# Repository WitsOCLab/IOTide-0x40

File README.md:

# IOTide-0x40
STM32 board with 64 powerful outputs to drive up to 16 (0x40) stepper motors.

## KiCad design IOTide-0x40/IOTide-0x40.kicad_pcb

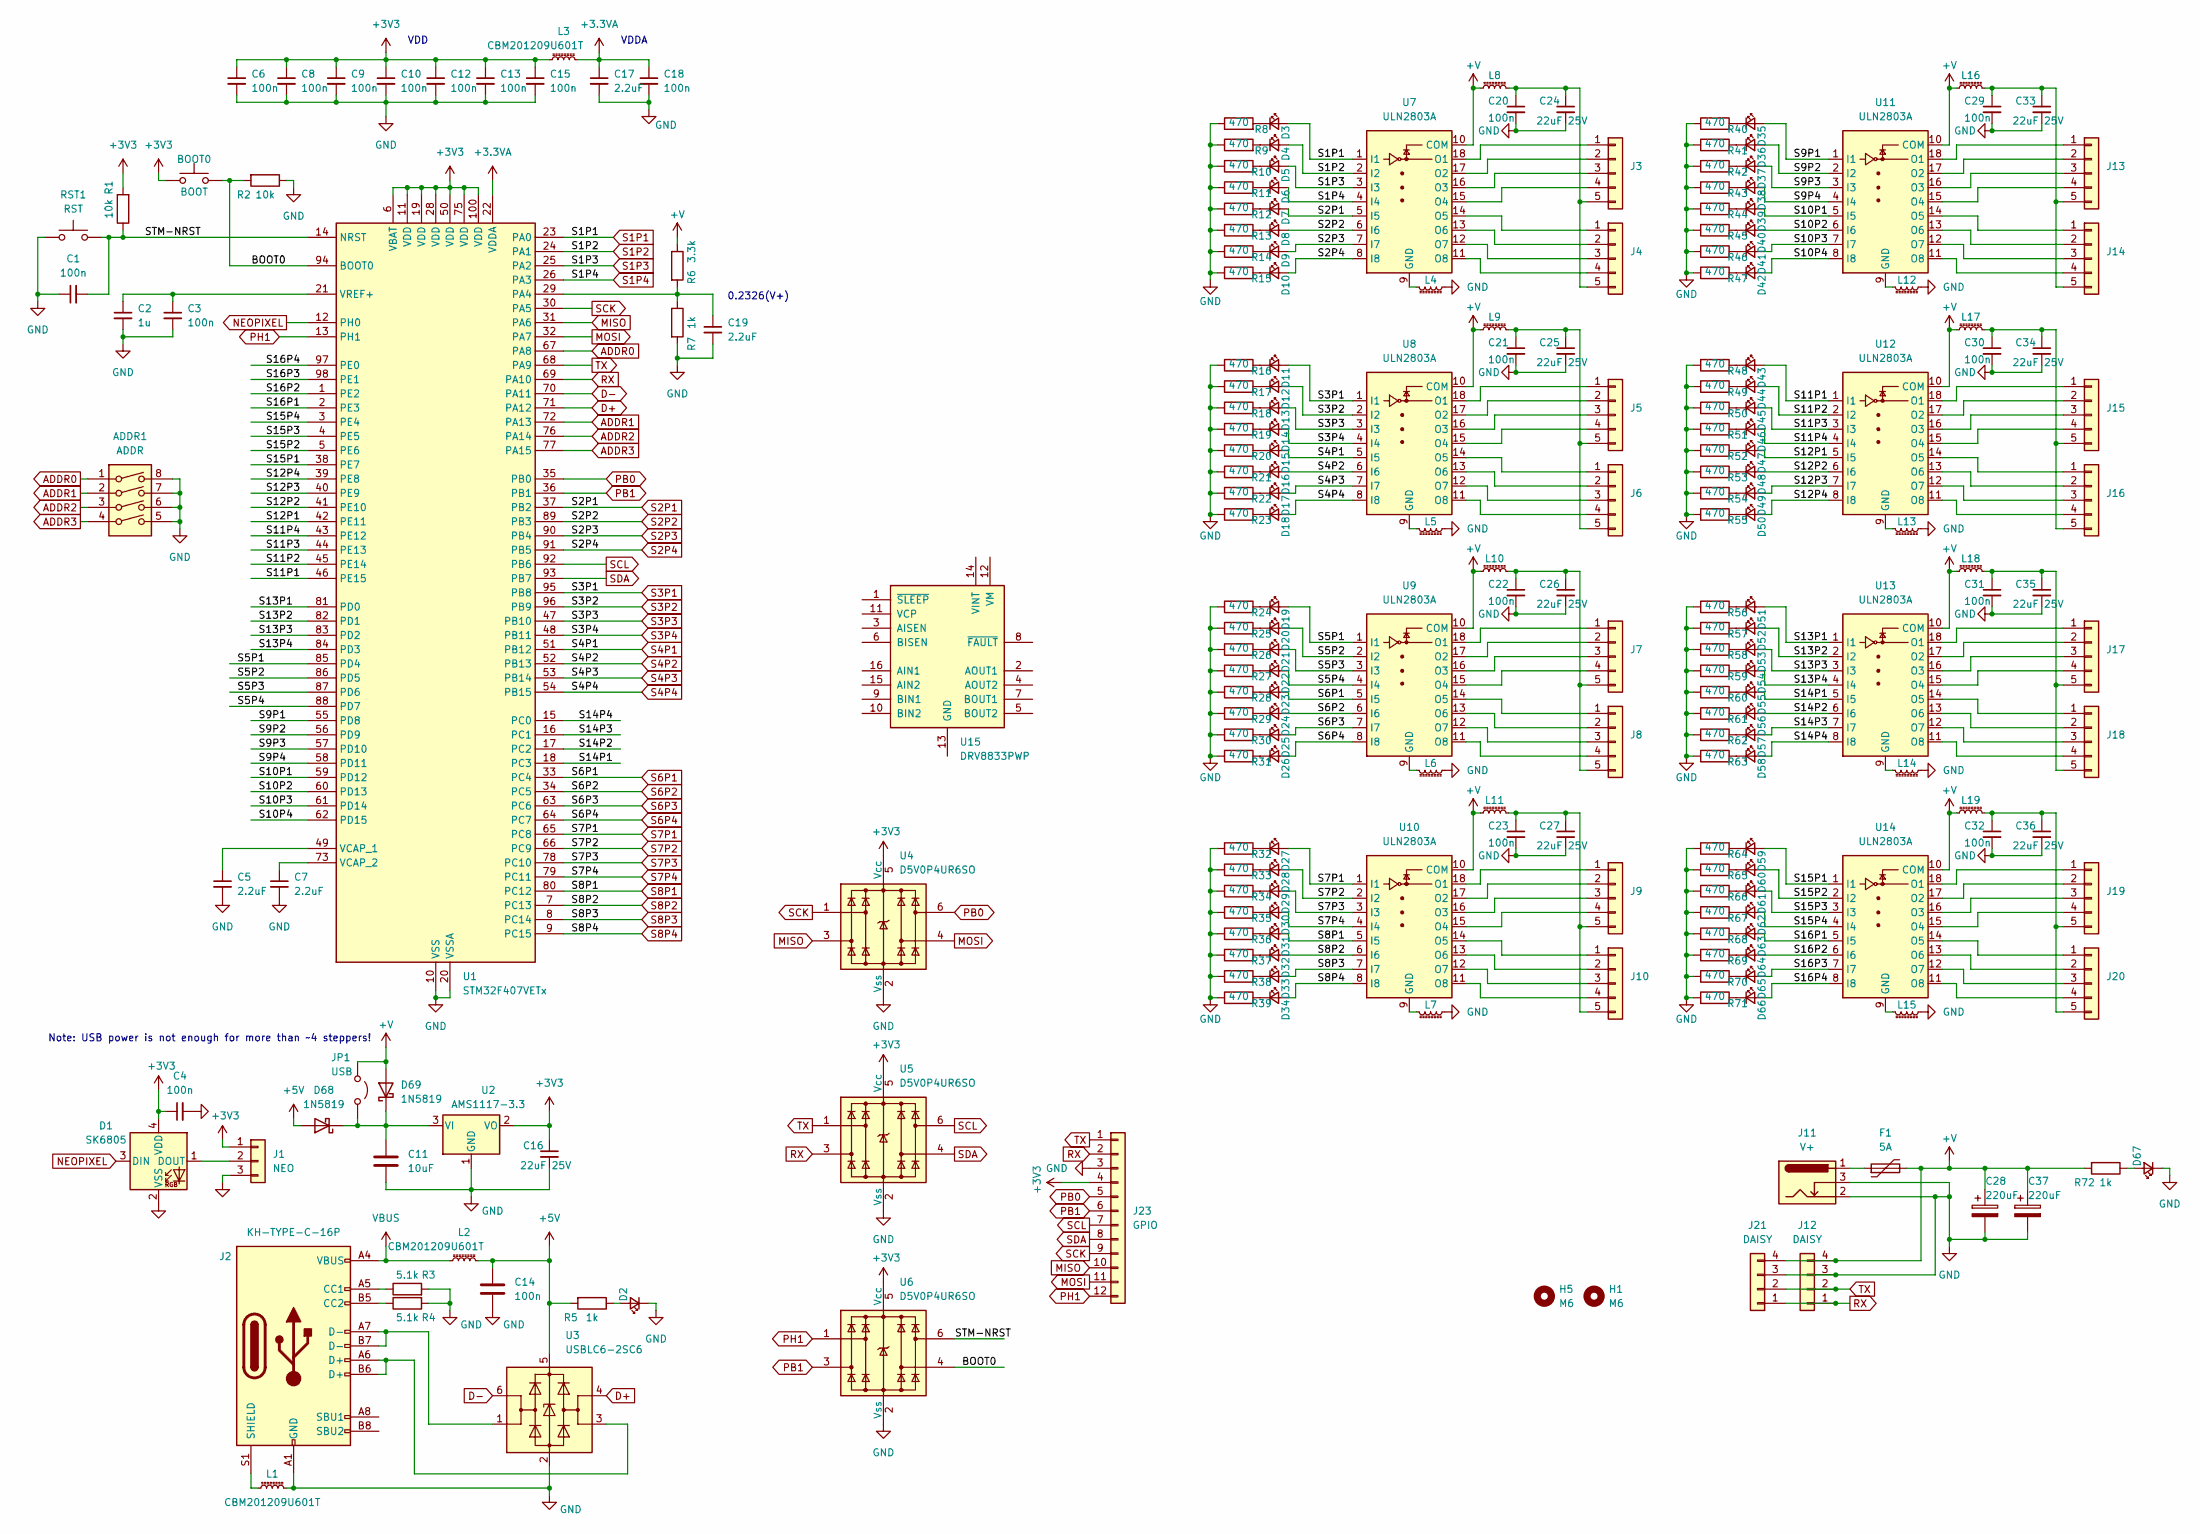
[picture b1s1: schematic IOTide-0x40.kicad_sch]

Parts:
ADDR1: ADDR; SW_DIP_SPSTx04_Slide_6.7x11.72mm_W6.73mm_P2.54mm_LowProfile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; LCSC C6331176
BOOT0: BOOT; SW_SPST_B3U-1000P-B; LCSC C720477
C1, C3, C4, C6, C8, C9, C10, C12, C13, C14, C15, C18, C20, C21, C22, C23, C29, C30, C31, C32: 100n; C_0402_1005Metric; LCSC C1525
C2: 1u; C_0402_1005Metric; LCSC C52923
C5, C7, C17, C19: 2.2uF; C_0402_1005Metric; LCSC C12530
C11: 10uF; C_0603_1608Metric; LCSC C96446
C16, C24, C25, C26, C27, C33, C34, C35, C36: 22uF 25V; C_0805_2012Metric; LCSC C45783
C28, C37: 220uF; CP_Elec_6.3x7.7; LCSC C7471881
D1: SK6805; LED_SK6805_PLCC4_2.4x2.7mm_P1.3mm; LCSC C2909056
D2, D67: BLUE; LED_0402_1005Metric; LCSC C130724
D3, D4, D5, D6, D7, D8, D9, D10, D11, D12, D13, D14, D15, D16, D17, D18, D19, D20, D21, D22, D23, D24, D25, D26, D27, D28, D29, D30, D31, D32, D33, D34, D35, D36, D37, D38, D39, D40, D41, D42, D43, D44, D45, D46, D47, D48, D49, D50, D51, D52, D53, D54, D55, D56, D57, D58, D59, D60, D61, D62, D63, D64, D65, D66: LED_Small; LED_0402_1005Metric; LCSC C130719
D68, D69: 1N5819; D_SOD-323; LCSC C191023
F1: 5A; Fuse_2920_7451Metric_Pad2.10x5.45mm_HandSolder; LCSC C20539728
H1, H5: M6; MountingHole_6.4mm_M6
J1: NEO; PinHeader_1x03_P2.54mm_Vertical
J2: KH-TYPE-C-16P; USB_C_Receptacle_GCT_USB4105-xx-A_16P_TopMnt_Horizontal; JLC C709357
J3: S1; JST_XH_B5B-XH-A_1x05_P2.50mm_Vertical; LCSC C161872
J4: S2; JST_XH_B5B-XH-A_1x05_P2.50mm_Vertical; LCSC C161872
J5, J6, J7, J8, J9, J10, J13, J14, J15, J16, J17, J18, J19, J20: Conn_01x05; JST_XH_B5B-XH-A_1x05_P2.50mm_Vertical; LCSC C161872
J11: V+; BarrelJack_Horizontal
J12, J21: DAISY; PinSocket_1x04_P2.54mm_Vertical
J23: GPIO; PinHeader_1x12_P2.54mm_Vertical
JP1: USB; SolderJumper-2_P1.3mm_Open_TrianglePad1.0x1.5mm
L1, L2, L3, L4, L5, L6, L7, L8, L9, L10, L11, L12, L13, L14, L15, L16, L17, L18, L19: CBM201209U601T; C_0805_2012Metric; LCSC C139168
R1, R2: 10k; R_0402_1005Metric; LCSC C25744
R3, R4: 5.1k; R_0402_1005Metric; LCSC C25905
R5, R72: 1k; R_0402_1005Metric; LCSC C25744
R6: 3.3k; R_0402_1005Metric; LCSC C25890
R7: 1k; R_0402_1005Metric; LCSC C11702
R8, R9, R10, R11, R12, R13, R14, R15, R16, R17, R18, R19, R20, R21, R22, R23, R24, R25, R26, R27, R28, R29, R30, R31, R32, R33, R34, R35, R36, R37, R38, R39, R40, R41, R42, R43, R44, R45, R46, R47, R48, R49, R50, R51, R52, R53, R54, R55, R56, R57, R58, R59, R60, R61, R62, R63, R64, R65, R66, R67, R68, R69, R70, R71: 470; R_0402_1005Metric; LCSC C25167
RST1: RST; SW_SPST_B3U-1000P-B; LCSC C720477
U1: STM32F407VETx; LQFP-100_14x14mm_P0.5mm; LCSC C28730
U2: AMS1117-3.3; SOT-89-3; LCSC C5120796
U3: USBLC6-2SC6; SOT-23-6; LCSC C2827654
U4, U5, U6: D5V0P4UR6SO; SOT-23-6; LCSC C531179
U7, U8, U9, U10, U11, U12, U13, U14: ULN2803A; SOP-18_7.495x11.515mm_P1.27mm; LCSC C845537
U15: DRV8833PWP; HTSSOP-16-1EP_4.4x5mm_P0.65mm_EP3.4x5mm_Mask2.46x2.31mm_The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

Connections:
+3.3VA: C17.1, C18.1, L3.2, U1.22 (VDDA)
+3V3: BOOT0.1, C4.1, C6.1, C8.1, C9.1, C10.1, C12.1, C13.1, C15.1, C16.1, D1.4 (VDD), J1.1, J23.4, L3.1, R1.2, U1.6 (VBAT), U1.11 (VDD), U1.19 (VDD), U1.28 (VDD), U1.50 (VDD), U1.75 (VDD), U1.100 (VDD), U2.2 (VO), U4.5 (Vcc), U5.5 (Vcc), U6.5 (Vcc)
+5V: C14.1, D68.2 (A), L2.2, R5.2, U3.5 (VBUS)
+V: C28.1, C37.1, D69.2 (A), F1.2, J12.4, J21.4, JP1.1 (A), L8.1, L9.1, L10.1, L11.1, L16.1, L17.1, L18.1, L19.1, R6.1, R72.2, U7.10 (COM), U8.10 (COM), U9.10 (COM), U10.10 (COM), U11.10 (COM), U12.10 (COM), U13.10 (COM), U14.10 (COM)
/BOOT0: BOOT0.2, R2.2, U1.94 (BOOT0), U6.4
/S5P1: D19.2 (A), U1.85 (PD4), U9.1 (I1)
/S5P2: D20.2 (A), U1.86 (PD5), U9.2 (I2)
/S5P3: D21.2 (A), U1.87 (PD6), U9.3 (I3)
/S5P4: D22.2 (A), U1.88 (PD7), U9.4 (I4)
/S9P1: D35.2 (A), U1.55 (PD8), U11.1 (I1)
/S9P2: D36.2 (A), U1.56 (PD9), U11.2 (I2)
/S9P3: D37.2 (A), U1.57 (PD10), U11.3 (I3)
/S9P4: D38.2 (A), U1.58 (PD11), U11.4 (I4)
/S10P1: D39.2 (A), U1.59 (PD12), U11.5 (I5)
/S10P2: D40.2 (A), U1.60 (PD13), U11.6 (I6)
/S10P3: D41.2 (A), U1.61 (PD14), U11.7 (I7)
/S10P4: D42.2 (A), U1.62 (PD15), U11.8 (I8)
/S11P1: D43.2 (A), U1.46 (PE15), U12.1 (I1)
/S11P2: D44.2 (A), U1.45 (PE14), U12.2 (I2)
/S11P3: D45.2 (A), U1.44 (PE13), U12.3 (I3)
/S11P4: D46.2 (A), U1.43 (PE12), U12.4 (I4)
/S12P1: D47.2 (A), U1.42 (PE11), U12.5 (I5)
/S12P2: D48.2 (A), U1.41 (PE10), U12.6 (I6)
/S12P3: D49.2 (A), U1.40 (PE9), U12.7 (I7)
/S12P4: D50.2 (A), U1.39 (PE8), U12.8 (I8)
/S13P1: D51.2 (A), U1.81 (PD0), U13.1 (I1)
/S13P2: D52.2 (A), U1.82 (PD1), U13.2 (I2)
/S13P3: D53.2 (A), U1.83 (PD2), U13.3 (I3)
/S13P4: D54.2 (A), U1.84 (PD3), U13.4 (I4)
/S14P1: D55.2 (A), U1.18 (PC3), U13.5 (I5)
/S14P2: D56.2 (A), U1.17 (PC2), U13.6 (I6)
/S14P3: D57.2 (A), U1.16 (PC1), U13.7 (I7)
/S14P4: D58.2 (A), U1.15 (PC0), U13.8 (I8)
/S15P1: D59.2 (A), U1.38 (PE7), U14.1 (I1)
/S15P2: D60.2 (A), U1.5 (PE6), U14.2 (I2)
/S15P3: D61.2 (A), U1.4 (PE5), U14.3 (I3)
/S15P4: D62.2 (A), U1.3 (PE4), U14.4 (I4)
/S16P1: D63.2 (A), U1.2 (PE3), U14.5 (I5)
/S16P2: D64.2 (A), U1.1 (PE2), U14.6 (I6)
/S16P3: D65.2 (A), U1.98 (PE1), U14.7 (I7)
/S16P4: D66.2 (A), U1.97 (PE0), U14.8 (I8)
/STM-NRST: C1.2, R1.1, RST1.2, U1.14 (NRST), U6.6
ADDR0: ADDR1.1, U1.67 (PA8)
ADDR1: ADDR1.2, U1.72 (PA13)
ADDR2: ADDR1.3, U1.76 (PA14)
ADDR3: ADDR1.4, U1.77 (PA15)
D+: U1.71 (PA12), U3.4 (I/O2)
D-: U1.70 (PA11), U3.6 (I/O1)
GND: ADDR1.5, ADDR1.6, ADDR1.7, ADDR1.8, C1.1, C2.2, C3.2, C4.2, C5.2, C6.2, C7.2, C8.2, C9.2, C10.2, C11.2, C12.2, C13.2, C14.2, C15.2, C16.2, C17.2, C18.2, C19.2, C20.2, C21.2, C22.2, C23.2, C24.2, C25.2, C26.2, C27.2, C28.2, C29.2, C30.2, C31.2, C32.2, C33.2, C34.2, C35.2, C36.2, C37.2, D1.2 (VSS), D2.1 (K), D67.1 (K), J1.3, J2.A1 (GND), J2.A12 (GND), J2.B1 (GND), J2.B12 (GND), J11.2, J11.3, J12.3, J21.3, J23.3, L1.2, L4.1, L5.1, L6.1, L7.1, L12.1, L13.1, L14.1, L15.1, R2.1, R3.2, R4.2, R7.2, R8.1, R9.1, R10.1, R11.1, R12.1, R13.1, R14.1, R15.1, R16.1, R17.1, R18.1, R19.1, R20.1, R21.1, R22.1, R23.1, R24.1, R25.1, R26.1, R27.1, R28.1, R29.1, R30.1, R31.1, R32.1, R33.1, R34.1, R35.1, R36.1, R37.1, R38.1, R39.1, R40.1, R41.1, R42.1, R43.1, R44.1, R45.1, R46.1, R47.1, R48.1, R49.1, R50.1, R51.1, R52.1, R53.1, R54.1, R55.1, R56.1, R57.1, R58.1, R59.1, R60.1, R61.1, R62.1, R63.1, R64.1, R65.1, R66.1, R67.1, R68.1, R69.1, R70.1, R71.1, RST1.1, U1.10 (VSS), U1.20 (VSSA), U1.27 (VSS), U1.74 (VSS), U1.99 (VSS), U2.1 (GND), U3.2 (GND), U4.2 (Vss), U5.2 (Vss), U6.2 (Vss)
MISO: J23.10, U1.31 (PA6), U4.3
MOSI: J23.11, U1.32 (PA7), U4.4
NEOPIXEL: D1.3 (DIN), U1.12 (PH0)
unnamed: D1.1 (DOUT), J1.2
unnamed: D2.2 (A), R5.1
unnamed: D3.1 (K), R8.2
unnamed: D4.1 (K), R9.2
unnamed: D5.1 (K), R10.2
unnamed: D6.1 (K), R11.2
unnamed: D7.1 (K), R12.2
unnamed: D8.1 (K), R13.2
unnamed: D9.1 (K), R14.2
unnamed: D10.1 (K), R15.2
unnamed: D11.1 (K), R16.2
unnamed: D12.1 (K), R17.2
unnamed: D13.1 (K), R18.2
unnamed: D14.1 (K), R19.2
unnamed: D15.1 (K), R20.2
unnamed: D16.1 (K), R21.2
unnamed: D17.1 (K), R22.2
unnamed: D18.1 (K), R23.2
unnamed: D19.1 (K), R24.2
unnamed: D20.1 (K), R25.2
unnamed: D21.1 (K), R26.2
unnamed: D22.1 (K), R27.2
unnamed: D23.1 (K), R28.2
unnamed: D24.1 (K), R29.2
unnamed: D25.1 (K), R30.2
unnamed: D26.1 (K), R31.2
unnamed: D27.1 (K), R32.2
unnamed: D28.1 (K), R33.2
unnamed: D29.1 (K), R34.2
unnamed: D30.1 (K), R35.2
unnamed: D31.1 (K), R36.2
unnamed: D32.1 (K), R37.2
unnamed: D33.1 (K), R38.2
unnamed: D34.1 (K), R39.2
unnamed: D35.1 (K), R40.2
unnamed: D36.1 (K), R41.2
unnamed: D37.1 (K), R42.2
unnamed: D38.1 (K), R43.2
unnamed: D39.1 (K), R44.2
unnamed: D40.1 (K), R45.2
unnamed: D41.1 (K), R46.2
unnamed: D42.1 (K), R47.2
unnamed: D43.1 (K), R48.2
unnamed: D44.1 (K), R49.2
unnamed: D45.1 (K), R50.2
unnamed: D46.1 (K), R51.2
unnamed: D47.1 (K), R52.2
unnamed: D48.1 (K), R53.2
unnamed: D49.1 (K), R54.2
unnamed: D50.1 (K), R55.2
unnamed: D51.1 (K), R56.2
unnamed: D52.1 (K), R57.2
unnamed: D53.1 (K), R58.2
unnamed: D54.1 (K), R59.2
unnamed: D55.1 (K), R60.2
unnamed: D56.1 (K), R61.2
unnamed: D57.1 (K), R62.2
unnamed: D58.1 (K), R63.2
unnamed: D59.1 (K), R64.2
unnamed: D60.1 (K), R65.2
unnamed: D61.1 (K), R66.2
unnamed: D62.1 (K), R67.2
unnamed: D63.1 (K), R68.2
unnamed: D64.1 (K), R69.2
unnamed: D65.1 (K), R70.2
unnamed: D66.1 (K), R71.2
unnamed: D67.2 (A), R72.1
unnamed: C11.1, D68.1 (K), D69.1 (K), JP1.2 (B), U2.3 (VI)
unnamed: F1.1, J11.1
unnamed: J2.A5 (CC1), R3.1
unnamed: J2.B5 (CC2), R4.1
unnamed: J2.A6 (D+), J2.B6 (D+), U3.3 (I/O2)
unnamed: J2.A7 (D-), J2.B7 (D-), U3.1 (I/O1)
unnamed: J2.S1 (SHIELD), L1.1
unnamed: J3.1, U7.18 (O1)
unnamed: J3.2, U7.17 (O2)
unnamed: J3.3, U7.16 (O3)
unnamed: J3.4, U7.15 (O4)
unnamed: C20.1, C24.1, J3.5, J4.5, L8.2
unnamed: J4.1, U7.14 (O5)
unnamed: J4.2, U7.13 (O6)
unnamed: J4.3, U7.12 (O7)
unnamed: J4.4, U7.11 (O8)
unnamed: J5.1, U8.18 (O1)
unnamed: J5.2, U8.17 (O2)
unnamed: J5.3, U8.16 (O3)
unnamed: J5.4, U8.15 (O4)
unnamed: C21.1, C25.1, J5.5, J6.5, L9.2
unnamed: J6.1, U8.14 (O5)
unnamed: J6.2, U8.13 (O6)
unnamed: J6.3, U8.12 (O7)
unnamed: J6.4, U8.11 (O8)
unnamed: J7.1, U9.18 (O1)
unnamed: J7.2, U9.17 (O2)
unnamed: J7.3, U9.16 (O3)
unnamed: J7.4, U9.15 (O4)
unnamed: C22.1, C26.1, J7.5, J8.5, L10.2
unnamed: J8.1, U9.14 (O5)
unnamed: J8.2, U9.13 (O6)
unnamed: J8.3, U9.12 (O7)
unnamed: J8.4, U9.11 (O8)
unnamed: J9.1, U10.18 (O1)
unnamed: J9.2, U10.17 (O2)
unnamed: J9.3, U10.16 (O3)
unnamed: J9.4, U10.15 (O4)
unnamed: J10.1, U10.14 (O5)
unnamed: J10.2, U10.13 (O6)
unnamed: J10.3, U10.12 (O7)
unnamed: J10.4, U10.11 (O8)
unnamed: C23.1, C27.1, J9.5, J10.5, L11.2
unnamed: J13.1, U11.18 (O1)
unnamed: J13.2, U11.17 (O2)
unnamed: J13.3, U11.16 (O3)
unnamed: J13.4, U11.15 (O4)
unnamed: C29.1, C33.1, J13.5, J14.5, L16.2
unnamed: J14.1, U11.14 (O5)
unnamed: J14.2, U11.13 (O6)
unnamed: J14.3, U11.12 (O7)
unnamed: J14.4, U11.11 (O8)
unnamed: J15.1, U12.18 (O1)
unnamed: J15.2, U12.17 (O2)
unnamed: J15.3, U12.16 (O3)
unnamed: J15.4, U12.15 (O4)
unnamed: C30.1, C34.1, J15.5, J16.5, L17.2
unnamed: J16.1, U12.14 (O5)
unnamed: J16.2, U12.13 (O6)
unnamed: J16.3, U12.12 (O7)
unnamed: J16.4, U12.11 (O8)
unnamed: J17.1, U13.18 (O1)
unnamed: J17.2, U13.17 (O2)
unnamed: J17.3, U13.16 (O3)
unnamed: J17.4, U13.15 (O4)
unnamed: C31.1, C35.1, J17.5, J18.5, L18.2
unnamed: J18.1, U13.14 (O5)
unnamed: J18.2, U13.13 (O6)
unnamed: J18.3, U13.12 (O7)
unnamed: J18.4, U13.11 (O8)
unnamed: J19.1, U14.18 (O1)
unnamed: J19.2, U14.17 (O2)
unnamed: J19.3, U14.16 (O3)
unnamed: J19.4, U14.15 (O4)
unnamed: C32.1, C36.1, J19.5, J20.5, L19.2
unnamed: J20.1, U14.14 (O5)
unnamed: J20.2, U14.13 (O6)
unnamed: J20.3, U14.12 (O7)
unnamed: J20.4, U14.11 (O8)
unnamed: C19.1, R6.2, R7.1, U1.29 (PA4)
unnamed: C5.1, U1.49 (VCAP_1)
unnamed: C7.1, U1.73 (VCAP_2)
unnamed: C2.1, C3.1, U1.21 (VREF+)
unnamed: L4.2, U7.9 (GND)
unnamed: L5.2, U8.9 (GND)
unnamed: L6.2, U9.9 (GND)
unnamed: L7.2, U10.9 (GND)
unnamed: L12.2, U11.9 (GND)
unnamed: L13.2, U12.9 (GND)
unnamed: L14.2, U13.9 (GND)
unnamed: L15.2, U14.9 (GND)
unnamed: U15.13 (GND), U15.17 (GND)
PB0: J23.5, U1.35 (PB0), U4.6
PB1: J23.6, U1.36 (PB1), U6.3
PH1: J23.12, U1.13 (PH1), U6.1
RX: J12.1, J21.1, J23.2, U1.69 (PA10), U5.3
S1P1: D3.2 (A), U1.23 (PA0), U7.1 (I1)
S1P2: D4.2 (A), U1.24 (PA1), U7.2 (I2)
S1P3: D5.2 (A), U1.25 (PA2), U7.3 (I3)
S1P4: D6.2 (A), U1.26 (PA3), U7.4 (I4)
S2P1: D7.2 (A), U1.37 (PB2), U7.5 (I5)
S2P2: D8.2 (A), U1.89 (PB3), U7.6 (I6)
S2P3: D9.2 (A), U1.90 (PB4), U7.7 (I7)
S2P4: D10.2 (A), U1.91 (PB5), U7.8 (I8)
S3P1: D11.2 (A), U1.95 (PB8), U8.1 (I1)
S3P2: D12.2 (A), U1.96 (PB9), U8.2 (I2)
S3P3: D13.2 (A), U1.47 (PB10), U8.3 (I3)
S3P4: D14.2 (A), U1.48 (PB11), U8.4 (I4)
S4P1: D15.2 (A), U1.51 (PB12), U8.5 (I5)
S4P2: D16.2 (A), U1.52 (PB13), U8.6 (I6)
S4P3: D17.2 (A), U1.53 (PB14), U8.7 (I7)
S4P4: D18.2 (A), U1.54 (PB15), U8.8 (I8)
S6P1: D23.2 (A), U1.33 (PC4), U9.5 (I5)
S6P2: D24.2 (A), U1.34 (PC5), U9.6 (I6)
S6P3: D25.2 (A), U1.63 (PC6), U9.7 (I7)
S6P4: D26.2 (A), U1.64 (PC7), U9.8 (I8)
S7P1: D27.2 (A), U1.65 (PC8), U10.1 (I1)
S7P2: D28.2 (A), U1.66 (PC9), U10.2 (I2)
S7P3: D29.2 (A), U1.78 (PC10), U10.3 (I3)
S7P4: D30.2 (A), U1.79 (PC11), U10.4 (I4)
S8P1: D31.2 (A), U1.80 (PC12), U10.5 (I5)
S8P2: D32.2 (A), U1.7 (PC13), U10.6 (I6)
S8P3: D33.2 (A), U1.8 (PC14), U10.7 (I7)
S8P4: D34.2 (A), U1.9 (PC15), U10.8 (I8)
SCK: J23.9, U1.30 (PA5), U4.1
SCL: J23.7, U1.92 (PB6), U5.6
SDA: J23.8, U1.93 (PB7), U5.4
TX: J12.2, J21.2, J23.1, U1.68 (PA9), U5.1
VBUS: J2.A4 (VBUS), J2.A9 (VBUS), J2.B4 (VBUS), J2.B9 (VBUS), L2.1

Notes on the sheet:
Note: USB power is not enough for more than ~4 steppers!
VDD
0.2326(V+)
VDDA

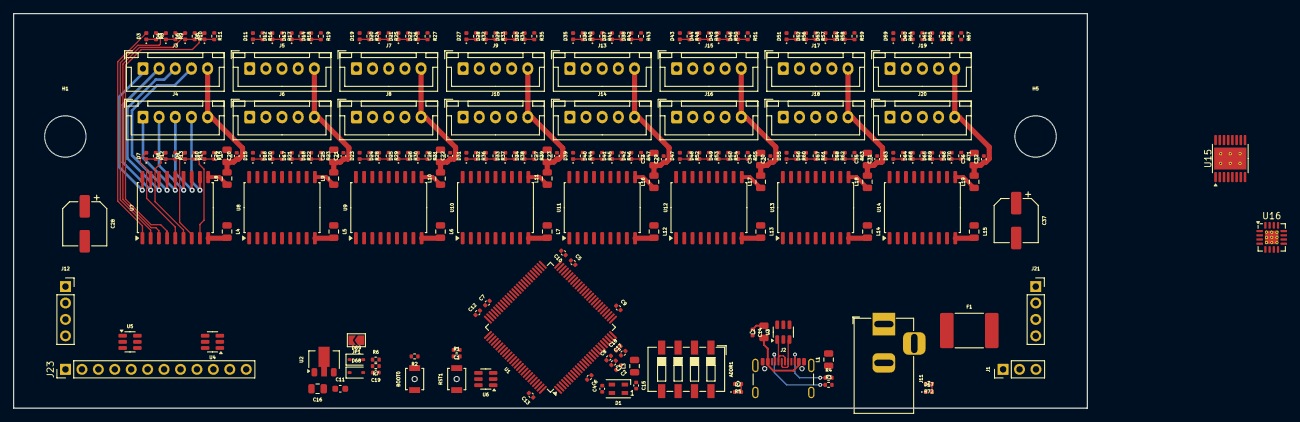
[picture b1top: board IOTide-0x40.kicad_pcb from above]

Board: 4 copper layers, 166.0 x 61.0 mm, 242 parts (0 on the bottom side), 249 nets.

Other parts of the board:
U16: DRV8833RTY; Texas_RTY_WQFN-16-1EP_4x4mm_P0.65mm_EP2.1x2.1mm_ThermalVias

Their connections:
unnamed: U16.11 (GND), U16.17 (GND)

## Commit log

2024-07-27 schematic done
